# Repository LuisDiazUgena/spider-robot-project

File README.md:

# spider-robot-project
Github repository for spider robot project by RegisHsu

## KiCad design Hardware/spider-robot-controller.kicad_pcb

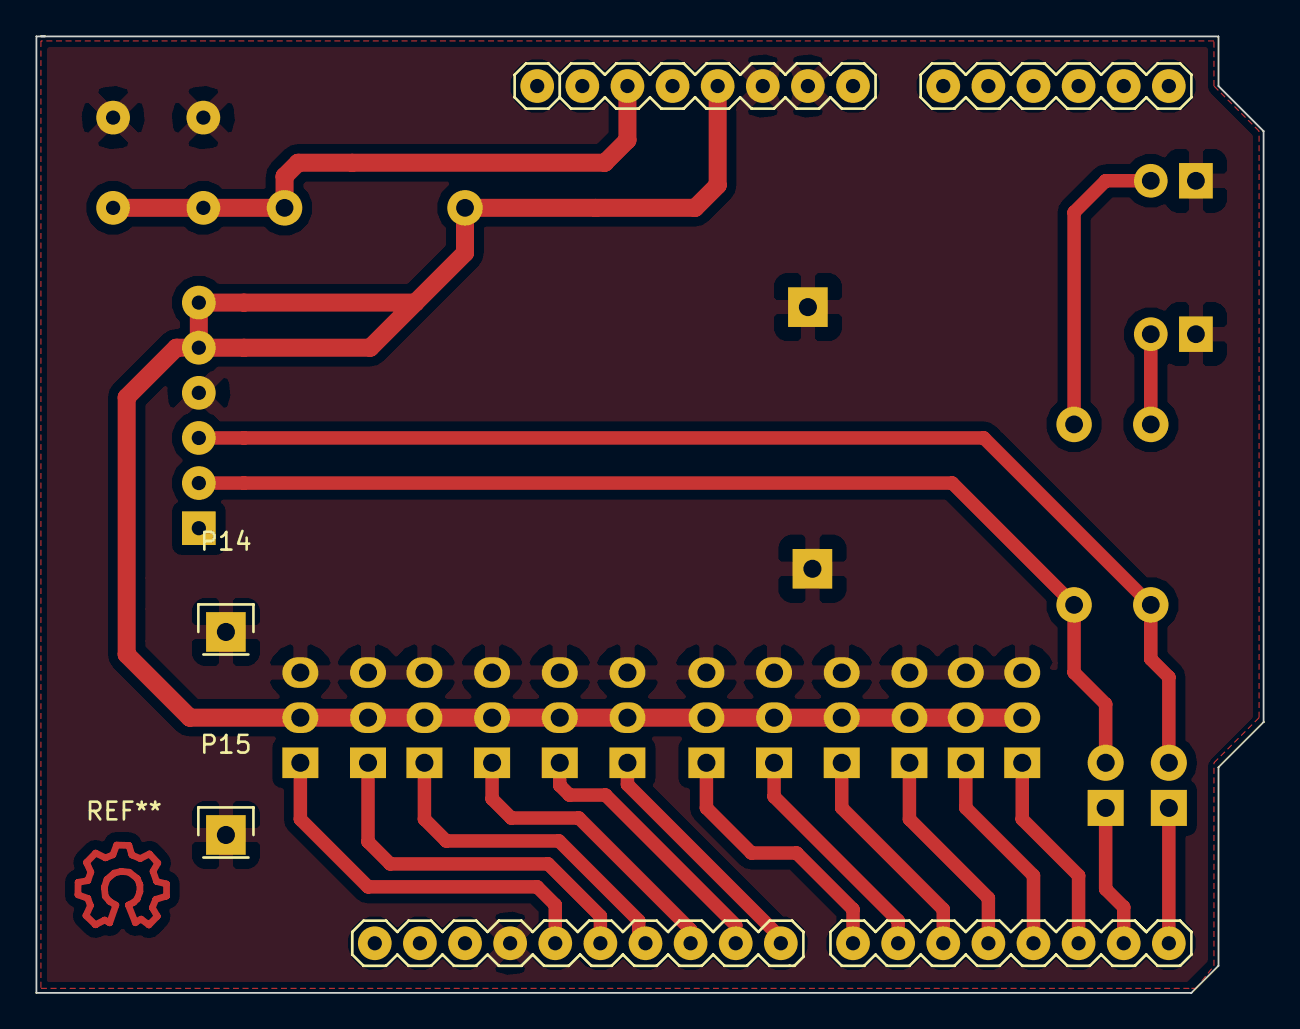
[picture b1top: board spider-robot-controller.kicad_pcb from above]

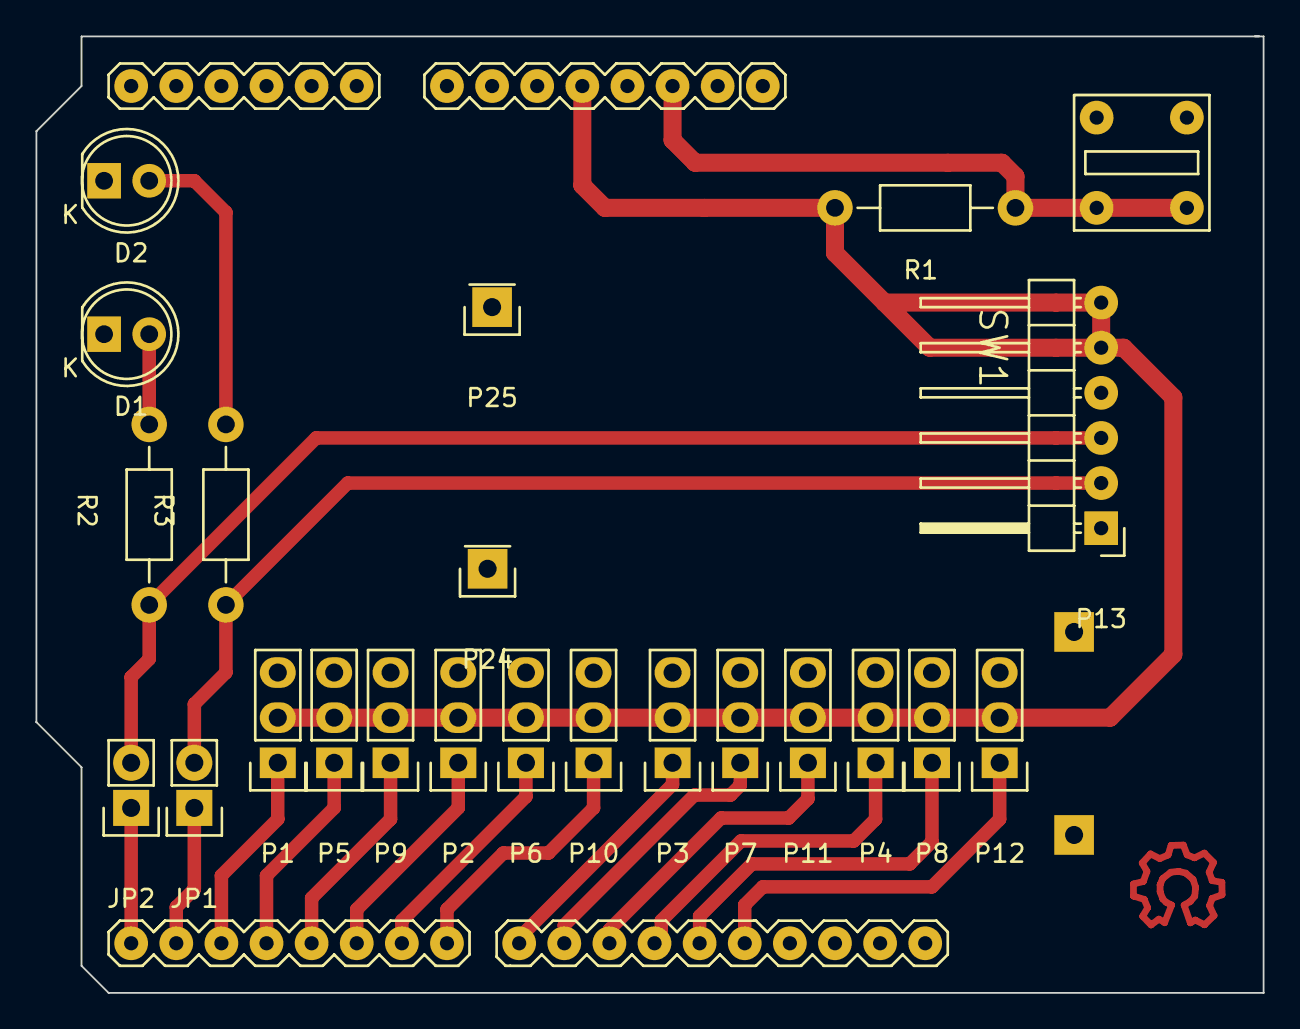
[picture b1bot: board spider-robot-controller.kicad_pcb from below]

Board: 2 copper layers, 69.1 x 53.8 mm, 26 parts (24 on the bottom side), 21 nets.

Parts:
D1: LED-TX; LED-5MM
D2: LED-RX; LED-5MM
JP1, JP2: JUMPER; Pin_Header_Straight_1x02
P1, P2, P3, P4, P5, P6, P7, P8, P9, P10, P11, P12: SERVO_HEADER; Pin_Header_Straight_1x03
P13: Bluetooth_header; Pin_Header_Angled_1x06
P14, P15, P24, P25: CONN_01X01; Pin_Header_Straight_1x01
R1: 10K; Resistor_Horizontal_RM10mm
R2, R3: 330; Resistor_Horizontal_RM10mm
SHIELD1: ARDUINO_SHIELD; ARDUINO_SHIELD_ROUNDPADS
SW1: SW_PUSH

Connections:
BRX: JP1.2, P13.2, R3.1
BTX: JP2.2, P13.3, R2.1
GND: D1.1, D2.1, P1.3, P2.3, P3.3, P4.3, P5.3, P6.3, P7.3, P8.3, P9.3, P10.3, P11.3, P12.3, P13.4, P14.1, P15.1, P24.1, P25.1, SHIELD1.GND1, SHIELD1.GND2, SHIELD1.GND3, SW1.2
unnamed: D1.2, R2.2
unnamed: D2.2, R3.2
unnamed: JP1.1, SHIELD1.1
unnamed: JP2.1, SHIELD1.0
RST: R1.1, SHIELD1.RST, SW1.1
S1: P1.1, SHIELD1.2
S2: P5.1, SHIELD1.3
S3: P9.1, SHIELD1.4
S4: P2.1, SHIELD1.5
S5: P6.1, SHIELD1.6
S6: P10.1, SHIELD1.7
S7: P3.1, SHIELD1.8
S8: P7.1, SHIELD1.9
S9: P11.1, SHIELD1.10
S10: P4.1, SHIELD1.11
S11: P8.1, SHIELD1.12
S12: P12.1, SHIELD1.13
VCC: P1.2, P2.2, P3.2, P4.2, P5.2, P6.2, P7.2, P8.2, P9.2, P10.2, P11.2, P12.2, P13.5, P13.6, R1.2, SHIELD1.5V

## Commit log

2015-09-16 Added libraries
2015-09-16 Added programmer, reset and servos circuits
2015-09-16 Added crystal
2015-09-16 added jack and removed wrong librearies
2015-09-16 added bluetooth & power circuit
2015-09-16 Removed unnecesary file
2015-09-16 Added atmega328dip and pushbutton switch footprints
2015-09-16 finished schematics
2015-09-16 Improved power circuit - added switch
2015-09-16 removed unnecesary libraries
2015-09-16 added permanent switch footprint
2015-09-16 working on pcb
2015-09-21 improved pcb layout traces
2015-09-21 updated license
2015-10-28 Added calibration sketch and movement-test sketch
2015-10-29 Added some movements
2015-10-29 Added movements
2015-10-29 position fixed
2015-11-02 Initial library work -untested
2015-11-02 Working on a sketch that includes the library
2015-11-02 Added test for add filaflex boots
2015-11-02 minor Improvements
2015-11-02 Now library works without any trouble
2015-11-02 Updated library
2015-11-02 Added some code for testing proposes
2015-11-03 Moved lib to another repo
2015-11-04 Removed old versions of boots
2015-11-04 Added new version of boots (V3)
2015-11-11 Changed from single board to a shield
2015-11-12 Improvements on the shield
2015-11-12 Added leds at bluetooth serial traces
2015-11-12 Added gerbers
2015-11-12 Improved layout of the board - BT module fits better
2015-11-12 updated gerbers
